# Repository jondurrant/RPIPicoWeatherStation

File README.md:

# RPIPicoWeatherStation
Raspberry Pi Pico W Weather Station

This project is a Weather Station powered by a Raspberry Pi Pico W. It is based on a Wind and Rain Sensors kit from [SparkFun](https://learn.sparkfun.com/tutorials/weather-meter-hookup-guide/all). Then adding additional sensors.

## Status
Project is still evolving and I am documenting the progress on my YouTube channel [drjonea](https://youtube.com/@drjonea).

Current status:
+ PCB First version is complete. This isn't perfect as some of the extension are not working as intended byt basic functions work
+ Code - Basic code to read and publish data to a webservice exist but is evolving
+ Server side code will be in a seperate repo and is work in progress right now

## PCB
The PCB folder contains a KiCAD model of schematic and board

Major components:
+ Raspberry Pi Pico W
+ Wind and Rain Sensor Kit [SparkFun](https://learn.sparkfun.com/tutorials/weather-meter-hookup-guide/all)
+ ChronoDot v2 DS3231 RTC
+ AHT10 Temperature and Humidity Sensor
+ SEN0500 [DFRobot](https://wiki.dfrobot.com/SKU_SEN0500_Fermion_Multifunctional_Environmental_Sensor) Composite sensor

## Tests
I use CPPUTest to build test framework. Currently these test are mainly about isolated testing of the component, to make sure each of the components on the board is working.

Tests can be found in the folder *test*. The test_main.cpp controls which tests are run.

## Exp
This contains some early experiments with the hardware and concepts.  Will probably be deleted at some point.

## Code
This is a Pico SDK and FreeRTOS Kernel application. It uses some of my own libraries for  Web Service publication.

## Build
Firmware can be build using the normal build process:
```
mkdir build
cd build
cmake ..
make
```

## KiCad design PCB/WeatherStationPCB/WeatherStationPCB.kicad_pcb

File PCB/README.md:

# Connections

<table>
  <tr><th>GPIO</th><th>NAME</th><th>Purpose</th></tr>
  <tr><td>0</td><td>UART0A_TX</td><td>Uart0 GP0 & FP1</td></tr>
  <tr><td>1</td><td>UART0A_RX</td><td></td></tr>
  <tr><td>2</td><td>SD_SCK</td><td>SPI For MicroSD Card</td></tr>
  <tr><td>3</td><td>SD_MOSI</td><td></td></tr>
  <tr><td>4</td><td>SD_MISO</td><td></td></tr>
  <tr><td>5</td><td>SD_CS</td><td></td></tr>
  
  <tr><td>6</td><td>Status Switch</td><td>Push to enable status</td></tr>
  <tr><td>7</td><td>LED_RED</td><td>Status LED</td></tr>
  <tr><td>10</td><td>LED_GRN</td><td></td></tr>
  <tr><td>11</td><td>LED_BLU</td><td></td></tr>
  
  <tr><td>8</td><td>UART1_TX</td><td>UART1 GP8 & 9</td></tr>
  <tr><td>9</td><td>UART1_RX</td><td></td></tr>
  
  <tr><td>12</td><td>SNT_CTR</td><td>SEN0500 and AMT10 Enable</td></tr>
  <tr><td>13</td><td>WIND_ANE</td><td>Anenometer switch</td></tr>
  <tr><td>14</td><td>WIND_VAP</td><td>Power for Weather Vane</td></tr>
  <tr><td>15</td><td>RAIN</td><td>Rain bucket switch</td></tr>
  
  <tr><td>16</td><td>UART0B_TX</td><td>UART0 GP16 & 17</td></tr>
  <tr><td>17</td><td>UART0B_RX</td><td> </td></tr>
  <tr><td>18</td><td>SDA1</td><td>I2C 1 For SEN0500 and AHT10 </td></tr>
  <tr><td>19</td><td>SCL1</td><td> </td></tr>
  <tr><td>20</td><td>SDA0</td><td>I2C for RTC DS3231</td></tr>
  <tr><td>21</td><td>SCL0</td><td></td></tr>
  
  <tr><td>22</td><td>I2C0_CTR</td><td>Power for DS3231 and External I2C0 Channels</td></tr>
  
  <tr><td>26</td><td>RTC_INT</td><td>DS3231 Interrupts</td></tr>
  <tr><td>27</td><td>RTC_BAT</td><td>DS3231 Battery Voltage </td></tr>
  <tr><td>28</td><td>WIND_VAD</td><td>Wind Vane Resistance</td></tr>
  
</table>

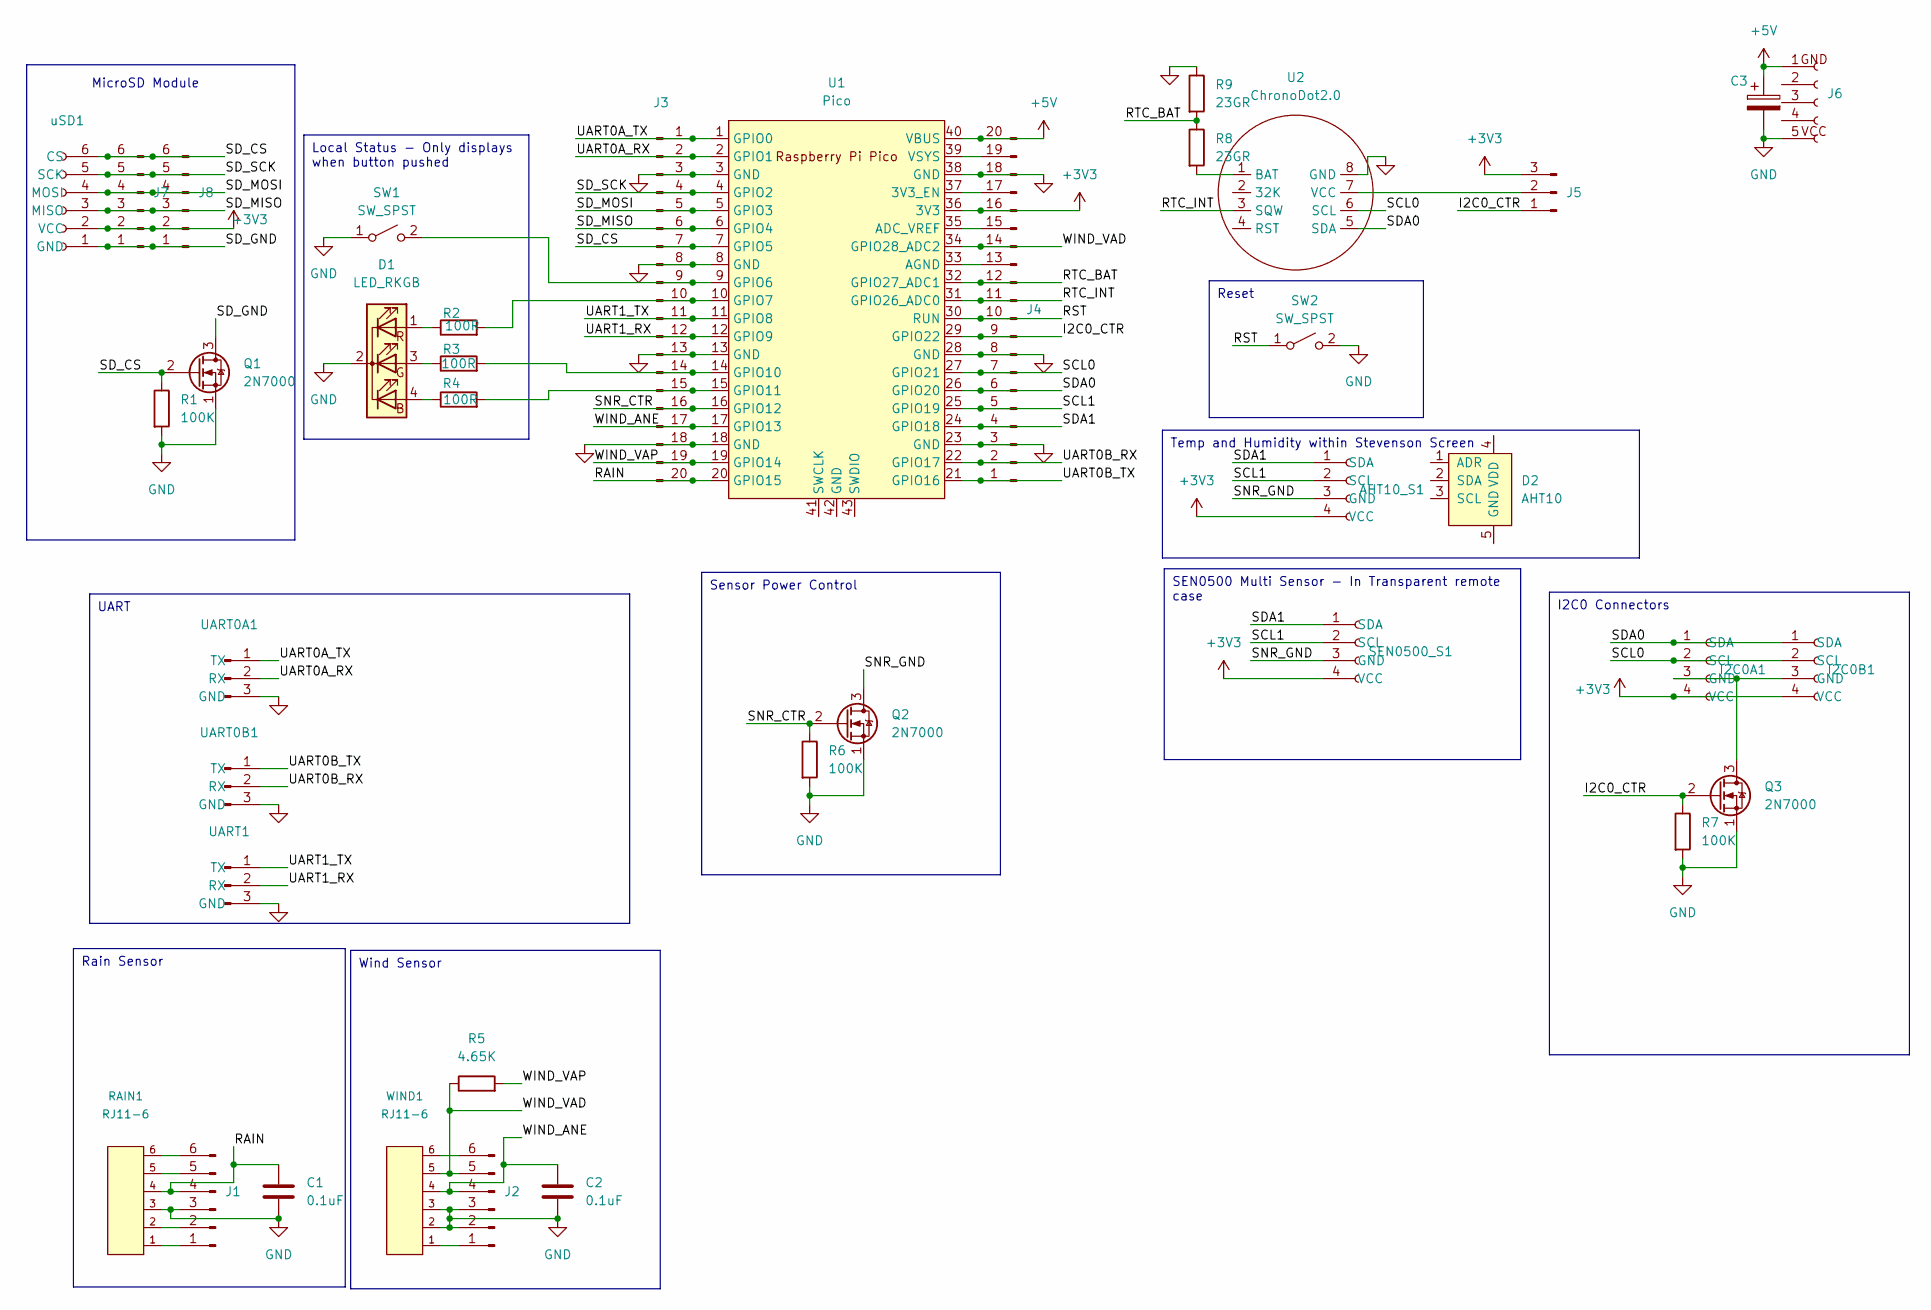
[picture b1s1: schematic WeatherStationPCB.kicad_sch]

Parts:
AHT10_S1: Conn_01x04_Socket; JST_XH_B4B-XH-AM_1x04_P2.50mm_Vertical
C1, C2: 0.1uF; C_Disc_D3.0mm_W1.6mm_P2.50mm
C3: C_Polarized; CP_Radial_D10.0mm_P5.00mm
D1: LED_RKGB; LED_D5.0mm-4_RGB
D2: AHT10
I2C0A1, I2C0B1: Conn_01x04_Socket; JST_XH_B4B-XH-AM_1x04_P2.50mm_Vertical
J1, J2: Conn_01x06_Male; PinHeader_1x06_P2.54mm_Vertical
J3, J4: Conn_01x20_Pin; PinHeader_1x20_P2.54mm_Vertical
J5: Conn_01x03_Pin; PinHeader_1x03_P2.54mm_Vertical
J6: Conn_01x05_Socket; PinSocket_1x05_P2.54mm_Horizontal
J7, J8: Conn_01x06_Pin; PinSocket_1x06_P2.54mm_Vertical
Q1, Q2, Q3: 2N7000; TO-92_Inline
R1, R6, R7: 100K; R_Axial_DIN0204_L3.6mm_D1.6mm_P5.08mm_Horizontal
R2, R3, R4: 100R; R_Axial_DIN0204_L3.6mm_D1.6mm_P5.08mm_Horizontal
R5: 4.65K; R_Axial_DIN0204_L3.6mm_D1.6mm_P5.08mm_Horizontal
R8, R9: 23GR; R_Axial_DIN0207_L6.3mm_D2.5mm_P10.16mm_Horizontal
RAIN1: RJ11-6
SEN0500_S1: Conn_01x04_Socket; JST_XH_B4B-XH-AM_1x04_P2.50mm_Vertical
SW1, SW2: SW_SPST; SW_PUSH_6mm
U1: Pico; RPi_Pico_SMD_TH
U2: ChronoDot2.0; ChronoDotV2
UART0A1, UART0B1, UART1: Conn_01x03_Pin; PinHeader_1x03_P2.54mm_Vertical
WIND1: RJ11-6
uSD1: Conn_01x06_Socket; PinSocket_1x06_P2.54mm_Horizontal

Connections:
+3V3: AHT10_S1.4 (VCC), I2C0A1.4 (VCC), I2C0B1.4 (VCC), J4.16, J5.3, J7.2, J8.2, SEN0500_S1.4 (VCC), U1.36 (3V3), uSD1.2 (VCC)
+5V: C3.1, J4.20, J6.1 (GND), U1.40 (VBUS)
/I2C0_CTR: J4.9, J5.1, Q3.2 (G), R7.1, U1.29 (GPIO22)
/RAIN: C1.1, J1.4, J3.20, RAIN1.4, U1.20 (GPIO15)
/RST: J4.10, SW2.1 (A), U1.30 (RUN)
/RTC_BAT: J4.12, R8.1, R9.2, U1.32 (GPIO27_ADC1)
/RTC_INT: J4.11, U1.31 (GPIO26_ADC0), U2.3 (SQW)
/SCL0: I2C0A1.2 (SCL), I2C0B1.2 (SCL), J4.7, U1.27 (GPIO21), U2.6 (SCL)
/SCL1: AHT10_S1.2 (SCL), J4.5, SEN0500_S1.2 (SCL), U1.25 (GPIO19)
/SDA0: I2C0A1.1 (SDA), I2C0B1.1 (SDA), J4.6, U1.26 (GPIO20), U2.5 (SDA)
/SDA1: AHT10_S1.1 (SDA), J4.4, SEN0500_S1.1 (SDA), U1.24 (GPIO18)
/SD_CS: J3.7, J7.6, J8.6, Q1.2 (G), R1.1, U1.7 (GPIO5), uSD1.6 (CS)
/SD_GND: J7.1, J8.1, Q1.3 (D), uSD1.1 (GND)
/SD_MISO: J3.6, J7.3, J8.3, U1.6 (GPIO4), uSD1.3 (MISO)
/SD_MOSI: J3.5, J7.4, J8.4, U1.5 (GPIO3), uSD1.4 (MOSI)
/SD_SCK: J3.4, J7.5, J8.5, U1.4 (GPIO2), uSD1.5 (SCK)
/SNR_CTR: J3.16, Q2.2 (G), R6.1, U1.16 (GPIO12)
/SNR_GND: AHT10_S1.3 (GND), Q2.3 (D), SEN0500_S1.3 (GND)
/UART0A_RX: J3.2, U1.2 (GPIO1), UART0A1.2 (RX)
/UART0A_TX: J3.1, U1.1 (GPIO0), UART0A1.1 (TX)
/UART0B_RX: J4.2, U1.22 (GPIO17), UART0B1.2 (RX)
/UART0B_TX: J4.1, U1.21 (GPIO16), UART0B1.1 (TX)
/UART1_RX: J3.12, U1.12 (GPIO9), UART1.2 (RX)
/UART1_TX: J3.11, U1.11 (GPIO8), UART1.1 (TX)
/WIND_ANE: C2.1, J2.4, J3.17, U1.17 (GPIO13), WIND1.4
/WIND_VAD: J2.5, J4.14, R5.1, U1.34 (GPIO28_ADC2), WIND1.5
/WIND_VAP: J3.19, R5.2, U1.19 (GPIO14)
GND: C1.2, C2.2, C3.2, D1.2 (K), J1.3, J2.2, J2.3, J3.3, J3.8, J3.13, J3.18, J4.3, J4.8, J4.18, J6.5 (VCC), Q1.1 (S), Q2.1 (S), Q3.1 (S), R1.2, R6.2, R7.2, R9.1, RAIN1.3, SW1.1 (A), SW2.2 (B), U1.3 (GND), U1.8 (GND), U1.13 (GND), U1.18 (GND), U1.23 (GND), U1.28 (GND), U1.38 (GND), U2.8 (GND), UART0A1.3 (GND), UART0B1.3 (GND), UART1.3 (GND), WIND1.2, WIND1.3
unnamed: D1.4 (BA), R4.1
unnamed: D1.3 (GA), R3.1
unnamed: D1.1 (RA), R2.1
unnamed: I2C0A1.3 (GND), I2C0B1.3 (GND), Q3.3 (D)
unnamed: J1.1, RAIN1.1
unnamed: J1.2, RAIN1.2
unnamed: J1.5, RAIN1.5
unnamed: J1.6, RAIN1.6
unnamed: J2.1, WIND1.1
unnamed: J2.6, WIND1.6
unnamed: J3.9, SW1.2 (B), U1.9 (GPIO6)
unnamed: J3.10, R2.2, U1.10 (GPIO7)
unnamed: J3.14, R3.2, U1.14 (GPIO10)
unnamed: J3.15, R4.2, U1.15 (GPIO11)
unnamed: J4.13, U1.33 (AGND)
unnamed: J4.15, U1.35 (ADC_VREF)
unnamed: J4.17, U1.37 (3V3_EN)
unnamed: J4.19, U1.39 (VSYS)
unnamed: J5.2, U2.7 (VCC)
unnamed: R8.2, U2.1 (BAT)

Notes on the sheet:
SEN0500 Multi Sensor - In Transparent remote case
Local Status - Only displays when button pushed
Sensor Power Control
Rain Sensor
I2C0 Connectors
UART
Temp and Humidity within Stevenson Screen
Wind Sensor
Reset
MicroSD Module

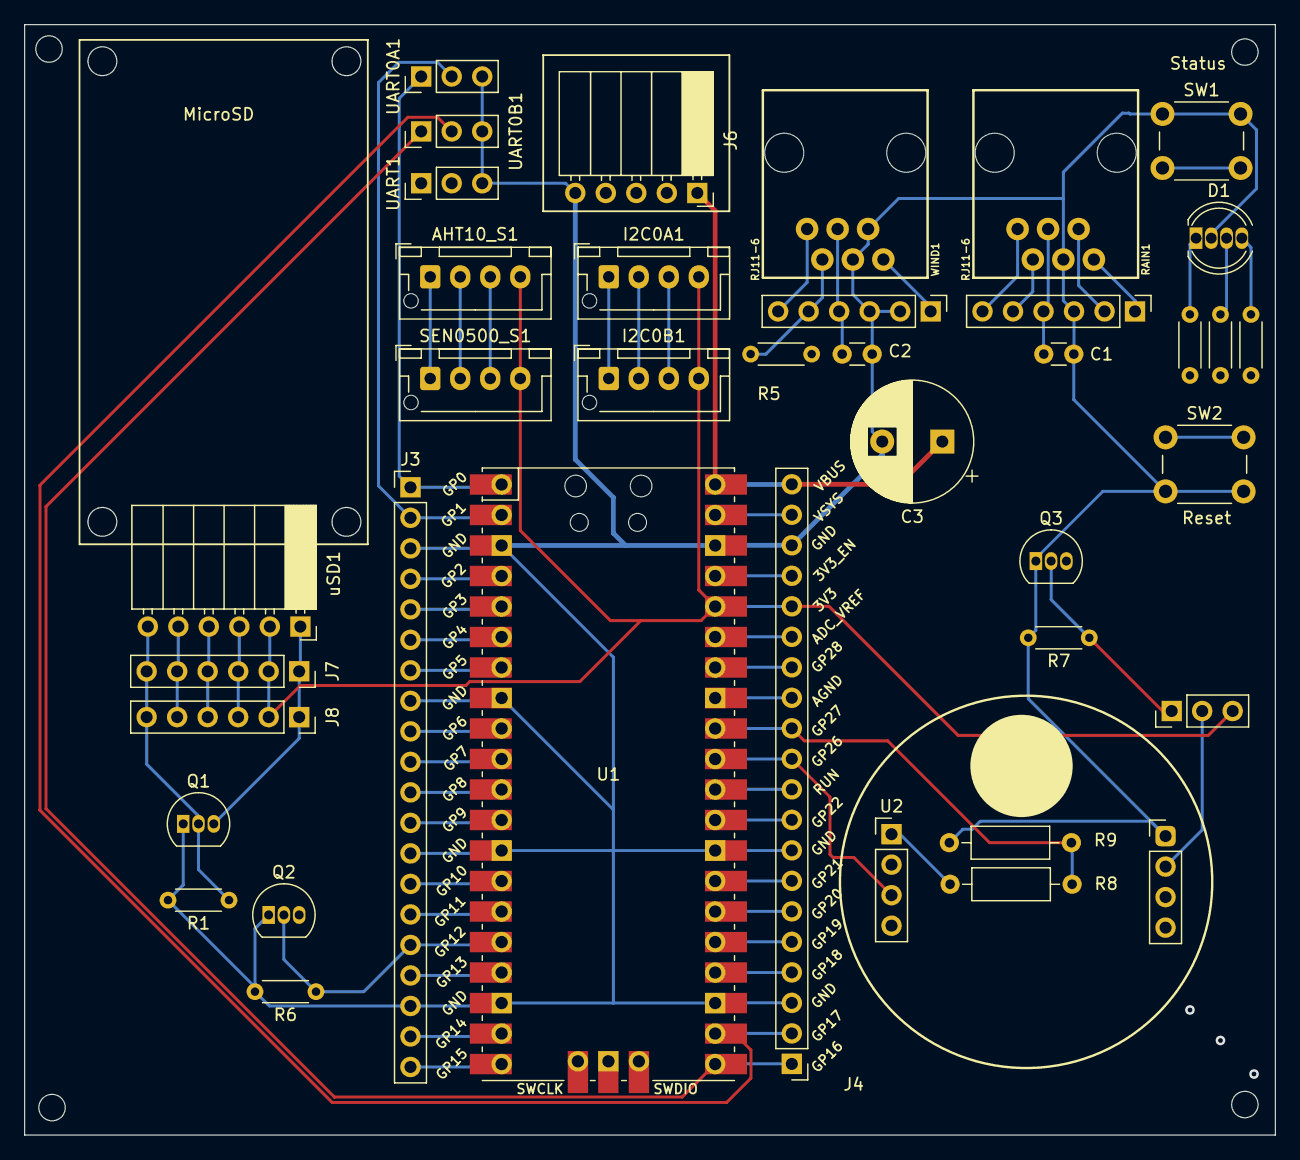
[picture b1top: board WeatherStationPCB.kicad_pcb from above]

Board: 4 copper layers, 104.1 x 92.5 mm, 38 parts (0 on the bottom side), 48 nets.

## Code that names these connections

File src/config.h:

/*
 * config.h
 *
 *  Created on: 13 Sept 2024
 *      Author: jondurrant
 */

#ifndef SRC_CONFIG_H_
#define SRC_CONFIG_H_

#define I2CCHAN i2c1
#define SDA1_PAD 18
#define SCL1_PAD 19

#define SDA0_PAD 20
#define SCL0_PAD 21
#define RTC_VCC 22
#define RTC_BAT 27

#define SWT_PAD 6
#define LED_PAD 7
#define RED_PAD 7
#define GRN_PAD 10
#define BLU_PAD 11


#define WAKE_PAD	26
#define ANEM_PAD 	13
#define DIRP_PAD 	   	14
#define DIRA_PAD    	28

#define SNR_CTR 12

#define RAIN 15



#endif /* SRC_CONFIG_H_ */

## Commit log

2024-07-12 Wind measurement expermiments
2024-07-15 Initial version of the Wind measurement
2024-07-16 Sleep and count while sleeping test
2024-07-22 Battery and Voltage
2024-08-06 SEN0500 over i2c
2024-08-06 Added SEN0500 control through 2N7000
2024-08-08 Added RTC
2024-08-08 Added power control for peripherals
2024-08-08 Turn on Vane power too
2024-08-15 Moved to FreeRTOS and added Status Agent
2024-08-15 RTOS Sleep plus wake by RTC or Switch
2024-09-05 Adding some test for the full hardware
2024-09-11 Added SEN0500 test
2024-09-12 WIP PAyload
2024-09-13 WIP Station control
2024-09-14 WIP SNTP and Wifi Init/DeInit
2024-09-15 AHT10 added to payload
2024-09-16 RTC as sensor
2024-09-16 Sen0500 added
2024-10-25 Added in sleep code to test cycle. TODO - HTTPS POST and HTTPS GET config
2024-11-08 Pico produces stats in simillar format to other sensors
2024-11-10 Move data to new JSON format
2024-11-14 Updating README before Video goes out today
2024-12-08 Added remote config download
2024-12-13 WIP. Has problems sleeping again, unsure why
2025-07-09 Licence correction
2025-07-09 Lib update
